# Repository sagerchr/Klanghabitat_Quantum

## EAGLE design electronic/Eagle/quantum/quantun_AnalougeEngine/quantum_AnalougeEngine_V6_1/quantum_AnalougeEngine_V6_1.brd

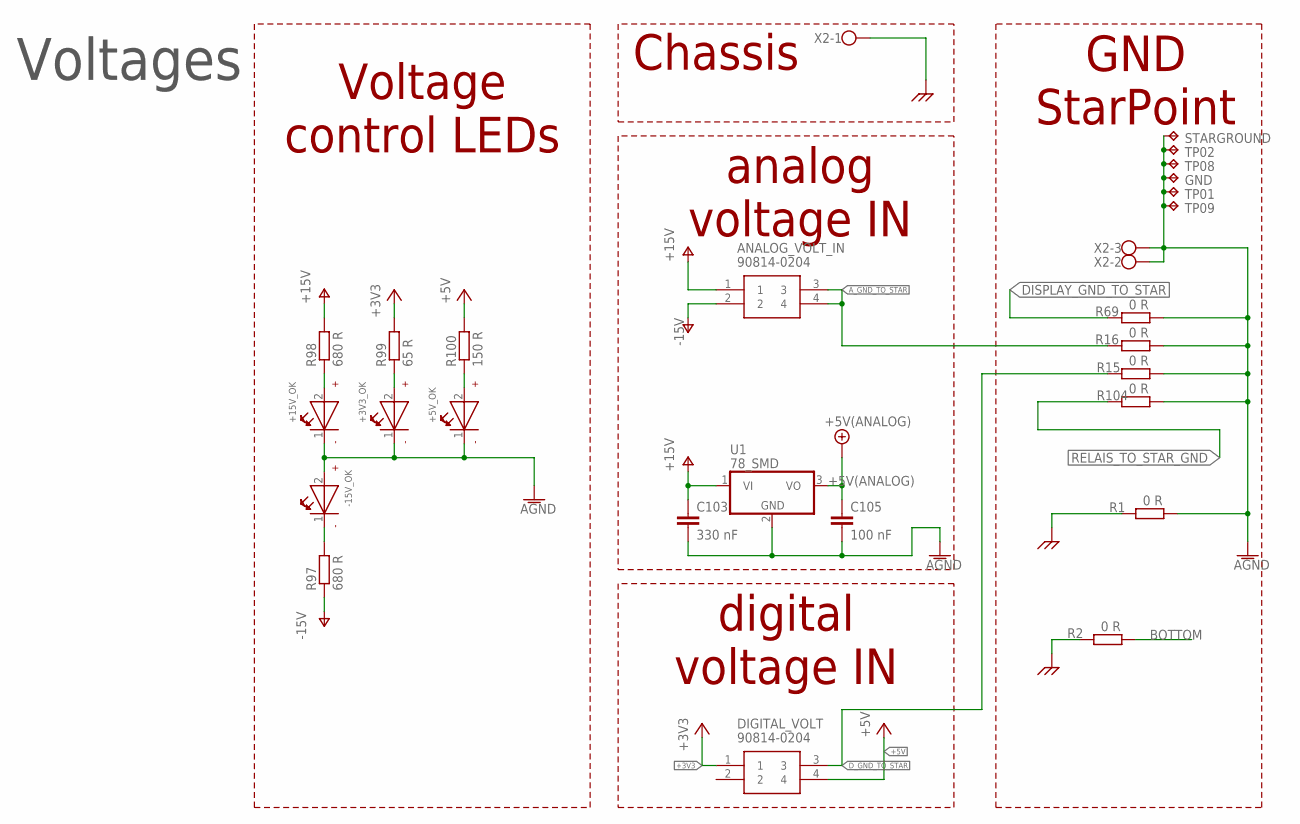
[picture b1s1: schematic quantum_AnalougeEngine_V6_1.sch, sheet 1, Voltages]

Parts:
+3V3_OK, +5V_OK, +15V_OK: LED_GREEN_SMD; WL-SMCW_0603
-15V_OK: LED_GREEN_SMD; WL-SMCW_0603
ANALOG_VOLT_IN: 90814-0204; MOLEX_90814-0204
C103: 330 nF; C0603
C105: 100 nF; C0603
DIGITAL_VOLT: 90814-0204; MOLEX_90814-0204
GND: TPTHT; THT_PIN
R1, R2, R15, R16, R69, R104: 0 R; R0603
R97, R98: 680 R; R0603
R99: 65 R; R0603
R100: 150 R; R0603
STARGROUND: TPTHT; THT_PIN
TP01, TP02, TP08, TP09: TPTHT; THT_PIN
U1: 78_SMD; TO252
X2: CONNECTOR_3POL; W237-103

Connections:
+3V3: DIGITAL_VOLT.1, R99.2; also elsewhere on the board
+5V: DIGITAL_VOLT.4, R100.2; also elsewhere on the board
+5V(ANALOG): C105.1, U1.3 (VO); also elsewhere on the board
AGND: +3V3_OK.1 (-), +5V_OK.1 (-), +15V_OK.1 (-), -15V_OK.2 (+), C103.2, C105.2, GND.P$1, R1.2, R15.2, R16.2, R69.2, R104.2, STARGROUND.P$1, TP01.P$1, TP02.P$1, TP08.P$1, TP09.P$1, U1.2 (GND), X2.2, X2.3; also elsewhere on the board
A_GND_TO_STAR: ANALOG_VOLT_IN.3, ANALOG_VOLT_IN.4, R16.1
BOTTOM: R2.2
CHASSIS: R1.1, R2.1, X2.1; also elsewhere on the board
DISPLAY_GND_TO_STAR: R69.1; also elsewhere on the board
D_GND_TO_STAR: DIGITAL_VOLT.3, R15.1
unnamed: -15V_OK.1 (-), R97.2
unnamed: +15V_OK.2 (+), R98.1
unnamed: +3V3_OK.2 (+), R99.1
unnamed: +5V_OK.2 (+), R100.1
RELAIS_TO_STAR_GND: R104.1; also elsewhere on the board
V+: ANALOG_VOLT_IN.1, C103.1, R98.2, U1.1 (VI); also elsewhere on the board
V-: ANALOG_VOLT_IN.2, R97.1; also elsewhere on the board

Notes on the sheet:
analog voltage IN
digital voltage IN
GND StarPoint
Chassis
Voltages
Voltage control LEDs

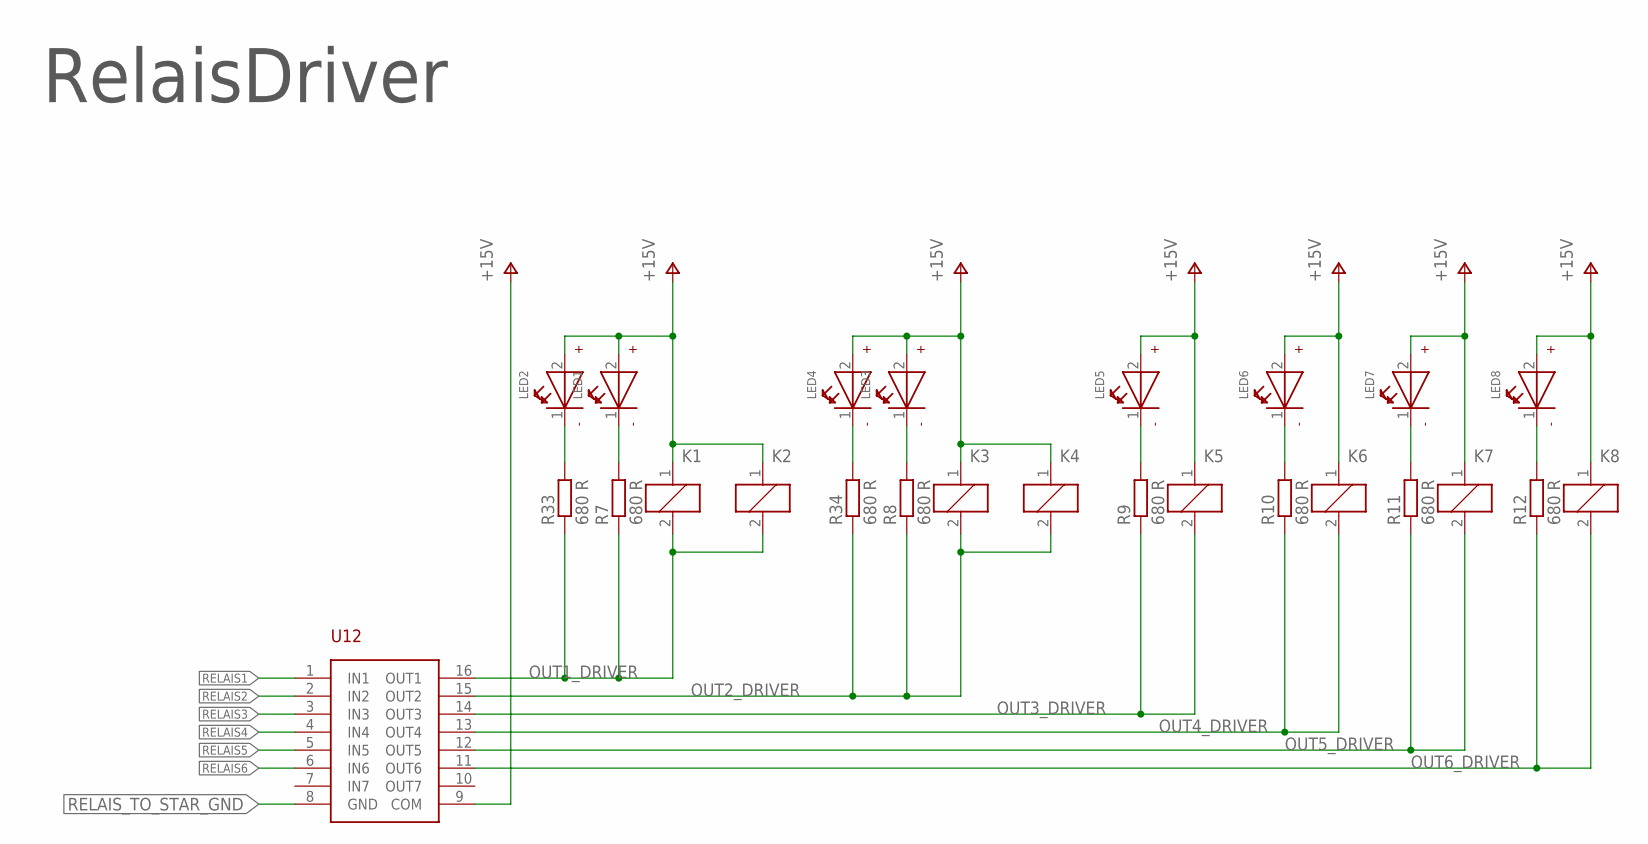
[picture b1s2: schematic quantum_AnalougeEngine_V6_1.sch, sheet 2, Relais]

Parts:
K1, K2, K3, K4, K5, K6, K7, K8: Relay; 351
LED1, LED2, LED3, LED4, LED5, LED6, LED7, LED8: LED_BLUE_SMD; WL-SMCW_0603
R7, R8, R9, R10, R11, R12, R33, R34: 680 R; R0603
U12: ULN2003; SOIC16

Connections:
unnamed: LED1.1 (-), R7.2
unnamed: LED3.1 (-), R8.2
unnamed: LED8.1 (-), R12.2
unnamed: LED7.1 (-), R11.2
unnamed: LED6.1 (-), R10.2
unnamed: LED5.1 (-), R9.2
unnamed: LED2.1 (-), R33.2
unnamed: LED4.1 (-), R34.2
OUT1_DRIVER: K1.2, K2.2, R7.1, R33.1, U12.16 (OUT1)
OUT2_DRIVER: K3.2, K4.2, R8.1, R34.1, U12.15 (OUT2)
OUT3_DRIVER: K5.2, R9.1, U12.14 (OUT3)
OUT4_DRIVER: K6.2, R10.1, U12.13 (OUT4)
OUT5_DRIVER: K7.2, R11.1, U12.12 (OUT5)
OUT6_DRIVER: K8.2, R12.1, U12.11 (OUT6)
RELAIS1: U12.1 (IN1); also elsewhere on the board
RELAIS2: U12.2 (IN2); also elsewhere on the board
RELAIS3: U12.3 (IN3); also elsewhere on the board
RELAIS4: U12.4 (IN4); also elsewhere on the board
RELAIS5: U12.5 (IN5); also elsewhere on the board
RELAIS6: U12.6 (IN6); also elsewhere on the board
RELAIS_TO_STAR_GND: U12.8 (GND); also elsewhere on the board
V+: K1.1, K2.1, K3.1, K4.1, K5.1, K6.1, K7.1, K8.1, LED1.2 (+), LED2.2 (+), LED3.2 (+), LED4.2 (+), LED5.2 (+), LED6.2 (+), LED7.2 (+), LED8.2 (+), U12.9 (COM); also elsewhere on the board

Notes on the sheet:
RelaisDriver

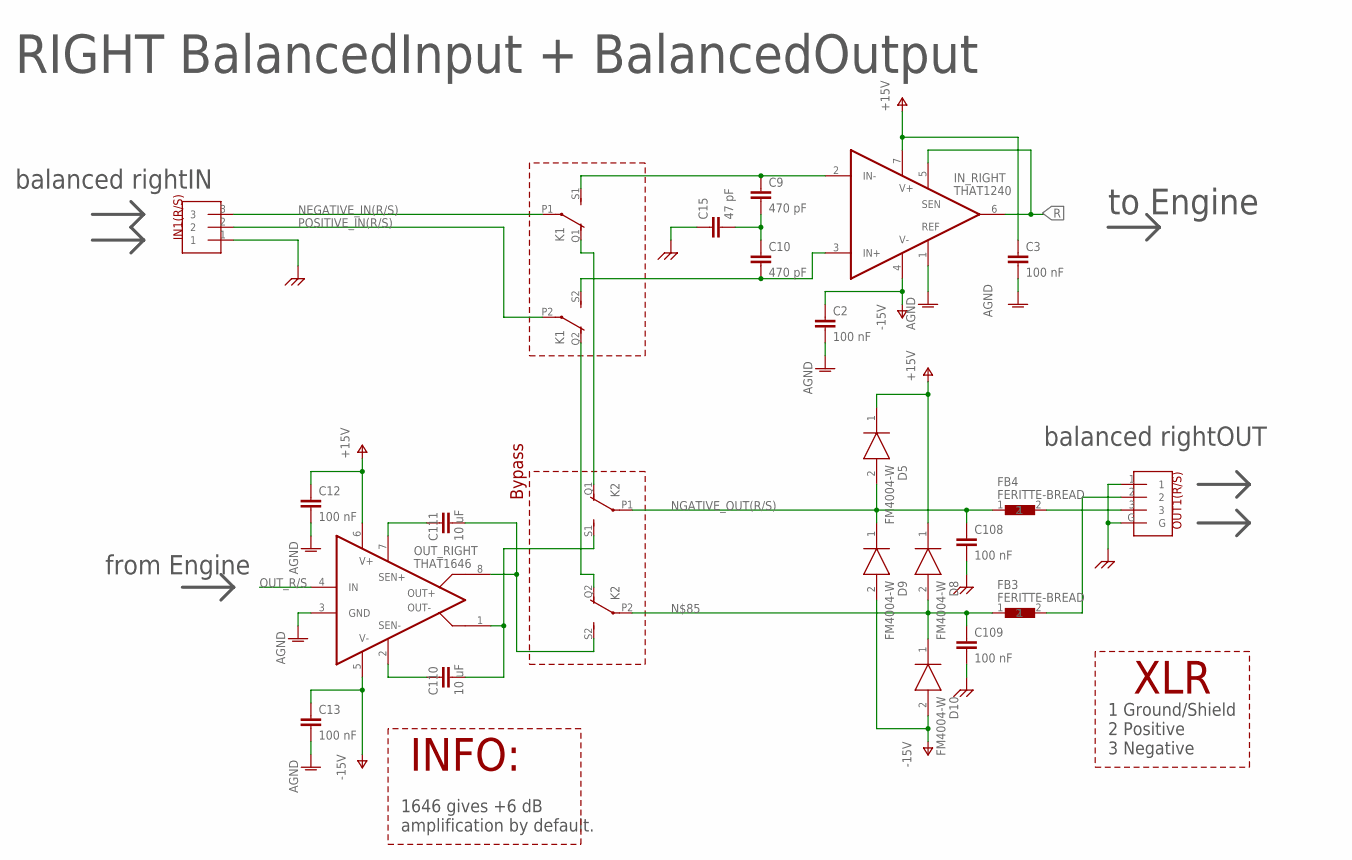
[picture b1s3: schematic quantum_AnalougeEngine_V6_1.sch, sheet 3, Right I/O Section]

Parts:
C2, C3, C12, C13, C108, C109: 100 nF; C0603
C9, C10: 470 pF; C0603
C15: 47 pF; C0603
C110, C111: 10 uF; C1206
D5, D8, D9, D10: FM4004-W; DIONM5025X231N
FB3, FB4: FERITTE-BREAD; BLM18KG102SH1J
IN1(R/S): NEUTRIK_NC3FAH
IN_RIGHT: THAT1240; SO08
K1, K2: Relay; 351
OUT1(R/S): NEUTRIK_NC3MAH
OUT_RIGHT: THAT1646; SO08

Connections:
AGND: C2.2, C3.2, C12.2, C13.2, IN_RIGHT.1 (REF), OUT_RIGHT.3 (GND); also elsewhere on the board
CHASSIS: C15.1, C108.2, C109.2, IN1(R/S).1, OUT1(R/S).1, OUT1(R/S).G; also elsewhere on the board
unnamed: C9.1, IN_RIGHT.2 (IN-), K1.S1 (S)
unnamed: C10.2, IN_RIGHT.3 (IN+), K1.S2 (S)
unnamed: C9.2, C10.1, C15.2
unnamed: K1.Q1 (O), K2.Q1 (O)
unnamed: K1.Q2 (O), K2.Q2 (O)
unnamed: FB4.2, OUT1(R/S).3
unnamed: C109.1, D8.2 (A), D10.1 (K), FB3.1, K2.P2
unnamed: C111.1, OUT_RIGHT.7 (SEN+)
unnamed: C110.1, OUT_RIGHT.2 (SEN-)
NEGATIVE_IN(R/S): IN1(R/S).3, K1.P1
NGATIVE_OUT(R/S): C108.1, D5.2 (A), D9.1 (K), FB4.1, K2.P1
OUT_R/S: OUT_RIGHT.4 (IN); also elsewhere on the board
POSITIVE_IN(R/S): IN1(R/S).2, K1.P2
POSITIVE_OUT(R/S): FB3.2, OUT1(R/S).2
R: IN_RIGHT.5 (SEN), IN_RIGHT.6 (OUT); also elsewhere on the board
R/S_OUT+: C111.2, K2.S2 (S), OUT_RIGHT.8 (OUT+)
R/S_OUT-: C110.2, K2.S1 (S), OUT_RIGHT.1 (OUT-)
V+: C3.1, C12.1, D5.1 (K), D8.1 (K), IN_RIGHT.7 (V+), OUT_RIGHT.6 (V+); also elsewhere on the board
V-: C2.1, C13.1, D9.2 (A), D10.2 (A), IN_RIGHT.4 (V-), OUT_RIGHT.5 (V-); also elsewhere on the board

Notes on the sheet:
RIGHT BalancedInput + BalancedOutput
balanced rightIN
balanced rightOUT
from Engine
to Engine
XLR
1 Ground/Shield 2 Positive 3 Negative
INFO:
1646 gives +6 dB amplification by default.
Bypass

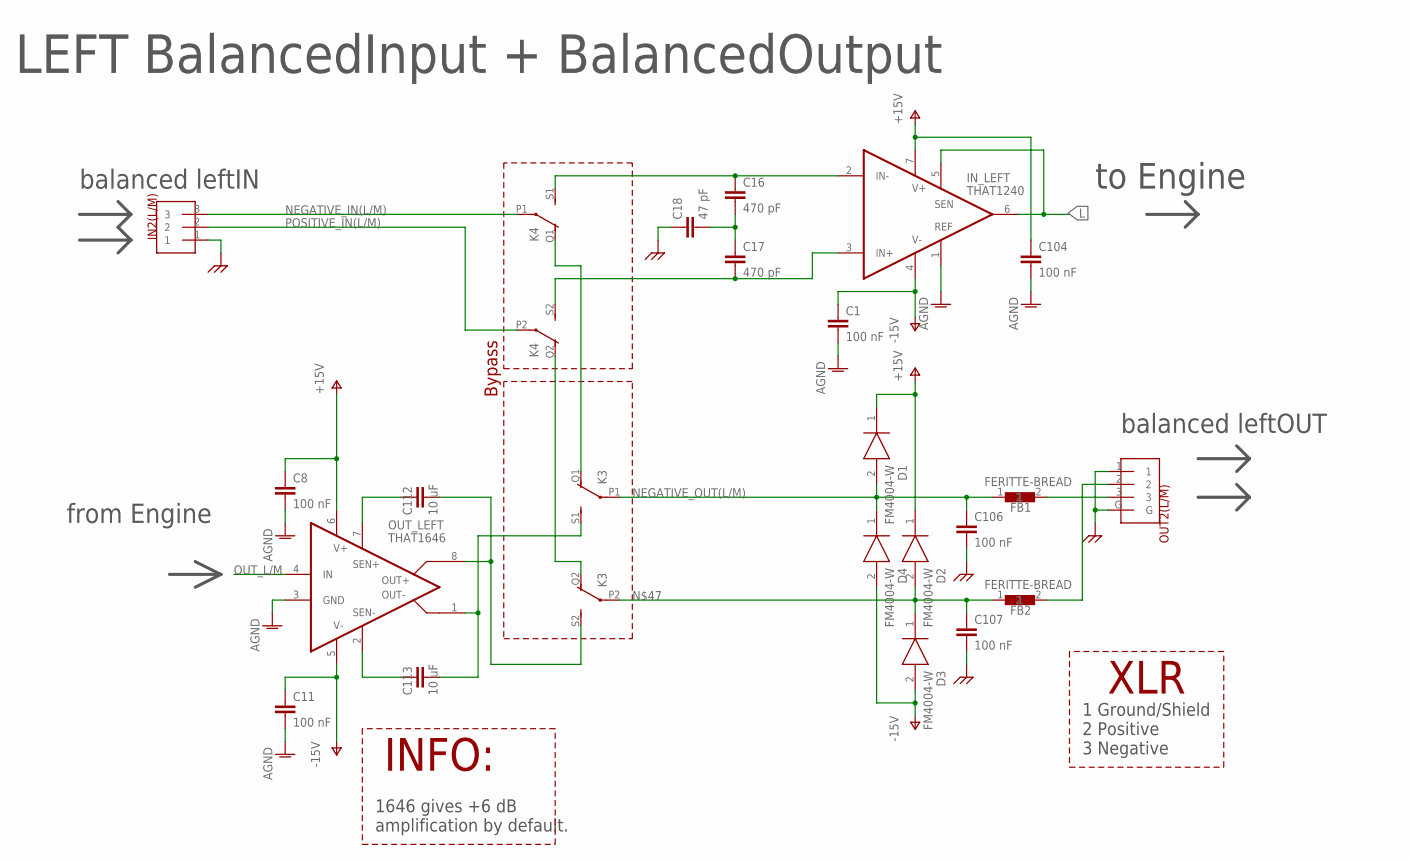
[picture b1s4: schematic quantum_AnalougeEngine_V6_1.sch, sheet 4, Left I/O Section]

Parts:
C1, C8, C11, C104, C106, C107: 100 nF; C0603
C16, C17: 470 pF; C0603
C18: 47 pF; C0603
C112, C113: 10 uF; C1206
D1, D2, D3, D4: FM4004-W; DIONM5025X231N
FB1, FB2: FERITTE-BREAD; BLM18KG102SH1J
IN2(L/M): NEUTRIK_NC3FAH
IN_LEFT: THAT1240; SO08
K3, K4: Relay; 351
OUT2(L/M): NEUTRIK_NC3MAH
OUT_LEFT: THAT1646; SO08

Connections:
AGND: C1.2, C8.2, C11.2, C104.2, IN_LEFT.1 (REF), OUT_LEFT.3 (GND); also elsewhere on the board
CHASSIS: C18.1, C106.2, C107.2, IN2(L/M).1, OUT2(L/M).1, OUT2(L/M).G; also elsewhere on the board
L: IN_LEFT.5 (SEN), IN_LEFT.6 (OUT); also elsewhere on the board
L/M_OUT+: C112.2, K3.S2 (S), OUT_LEFT.8 (OUT+)
L/M_OUT-: C113.2, K3.S1 (S), OUT_LEFT.1 (OUT-)
unnamed: C17.2, IN_LEFT.3 (IN+), K4.S2 (S)
unnamed: C16.2, C17.1, C18.2
unnamed: C16.1, IN_LEFT.2 (IN-), K4.S1 (S)
unnamed: K3.Q1 (O), K4.Q1 (O)
unnamed: K3.Q2 (O), K4.Q2 (O)
unnamed: FB1.2, OUT2(L/M).3
unnamed: C107.1, D2.2 (A), D3.1 (K), FB2.1, K3.P2
unnamed: C113.1, OUT_LEFT.2 (SEN-)
unnamed: C112.1, OUT_LEFT.7 (SEN+)
NEGATIVE_IN(L/M): IN2(L/M).3, K4.P1
NEGATIVE_OUT(L/M): C106.1, D1.2 (A), D4.1 (K), FB1.1, K3.P1
OUT_L/M: OUT_LEFT.4 (IN); also elsewhere on the board
POSITIVE_IN(L/M): IN2(L/M).2, K4.P2
POSITIVE_OUT(L/M): FB2.2, OUT2(L/M).2
V+: C8.1, C104.1, D1.1 (K), D2.1 (K), IN_LEFT.7 (V+), OUT_LEFT.6 (V+); also elsewhere on the board
V-: C1.1, C11.1, D3.2 (A), D4.2 (A), IN_LEFT.4 (V-), OUT_LEFT.5 (V-); also elsewhere on the board

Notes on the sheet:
balanced leftIN
balanced leftOUT
from Engine
to Engine
LEFT BalancedInput + BalancedOutput
XLR
1 Ground/Shield 2 Positive 3 Negative
INFO:
1646 gives +6 dB amplification by default.
Bypass

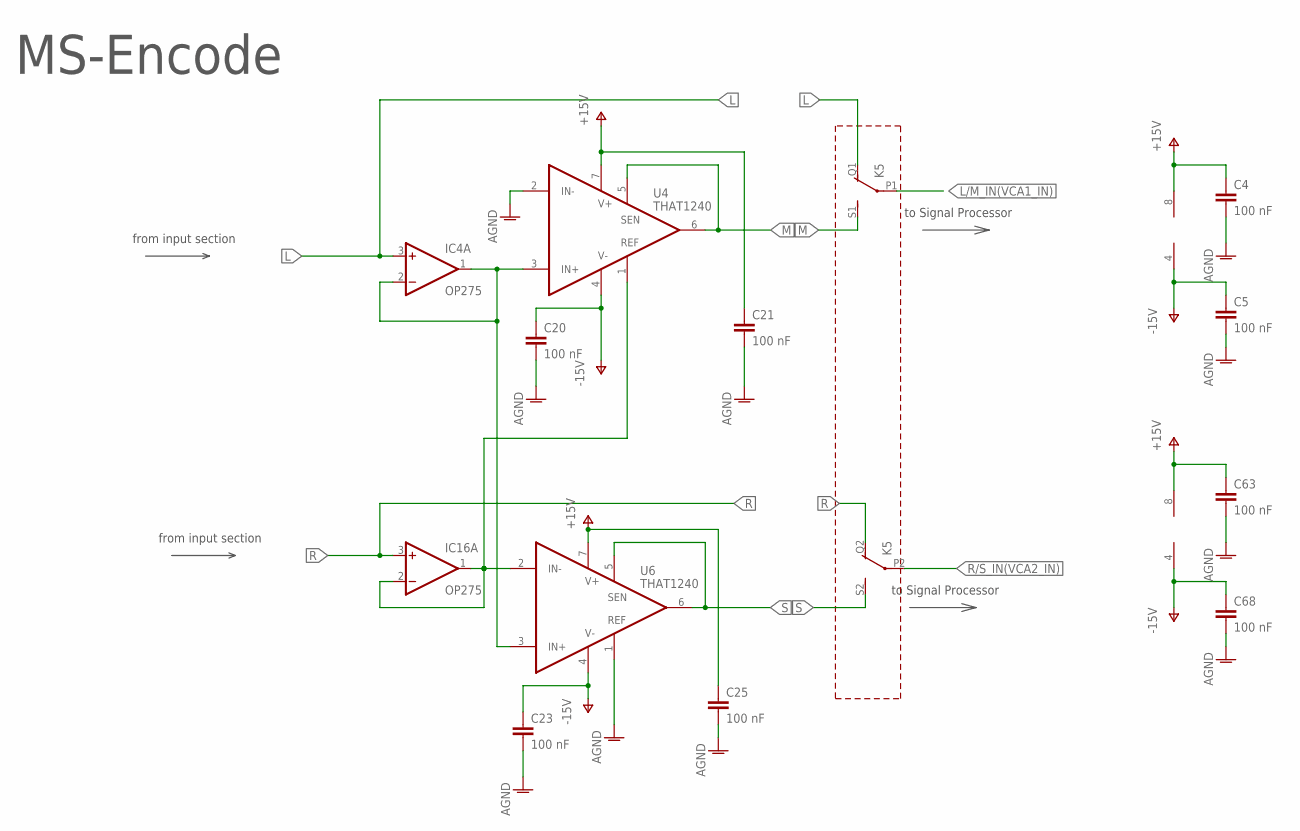
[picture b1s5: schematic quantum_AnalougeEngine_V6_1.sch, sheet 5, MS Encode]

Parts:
C4, C5, C20, C21, C23, C25, C63, C68: 100 nF; C0603
IC4, IC16: OP275; SOIC8
K5: Relay; 351
U4, U6: THAT1240; SO08

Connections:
AGND: C4.2, C5.2, C20.2, C21.2, C23.2, C25.2, C63.2, C68.2, U4.2 (IN-), U6.1 (REF); also elsewhere on the board
L: IC4.3 (+IN), K5.Q1 (O); also elsewhere on the board
L/M_IN(VCA1_IN): K5.P1; also elsewhere on the board
M: K5.S1 (S), U4.5 (SEN), U4.6 (OUT)
unnamed: IC4.1 (OUT), IC4.2 (-IN), U4.3 (IN+), U6.3 (IN+)
unnamed: IC16.1 (OUT), IC16.2 (-IN), U4.1 (REF), U6.2 (IN-)
R: IC16.3 (+IN), K5.Q2 (O); also elsewhere on the board
R/S_IN(VCA2_IN): K5.P2; also elsewhere on the board
S: K5.S2 (S), U6.5 (SEN), U6.6 (OUT)
V+: C4.1, C21.1, C25.1, C63.1, IC4.8 (V+), IC16.8 (V+), U4.7 (V+), U6.7 (V+); also elsewhere on the board
V-: C5.1, C20.1, C23.1, C68.1, IC4.4 (V-), IC16.4 (V-), U4.4 (V-), U6.4 (V-); also elsewhere on the board

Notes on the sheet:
to Signal Processor
MS-Encode
from input section

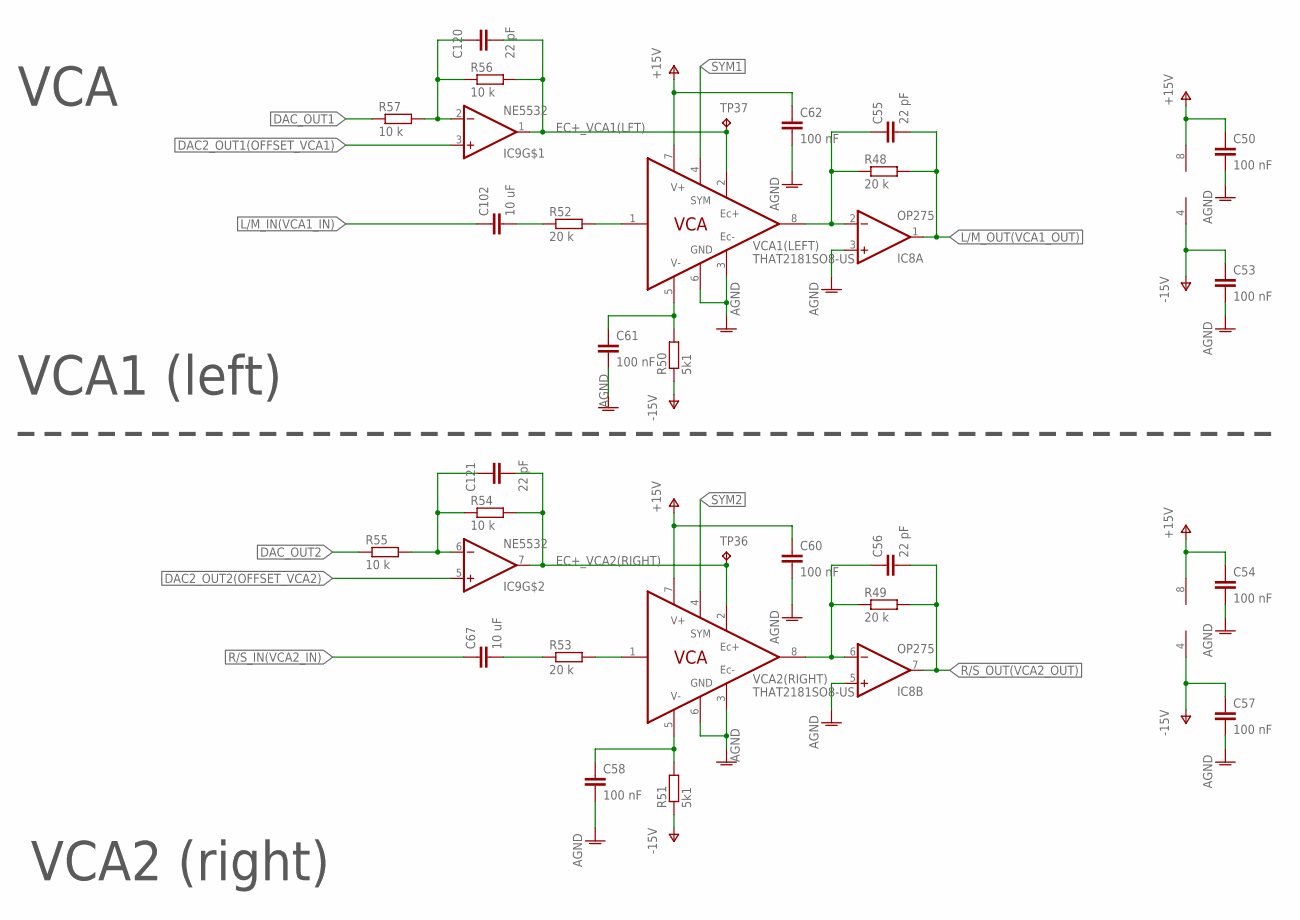
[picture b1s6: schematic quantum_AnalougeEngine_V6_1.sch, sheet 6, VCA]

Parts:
C50, C53, C54, C57, C58, C60, C61, C62: 100 nF; C0603
C55, C56, C120, C121: 22 pF; C0603
C67, C102: 10 uF; C1206
IC8: OP275; SOIC8
IC9: NE5532; SOIC8
R48, R49, R52, R53: 20 k; R0603
R50, R51: 5k1; R0603
R54, R55, R56, R57: 10 k; R0603
TP36, TP37: TPTHT; THT_PIN
VCA1(LEFT), VCA2(RIGHT): THAT2181SO8-US; SO08

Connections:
AGND: C50.2, C53.2, C54.2, C57.2, C58.2, C60.2, C61.2, C62.2, IC8.3 (+IN), IC8.5 (+IN), VCA1(LEFT).3 (EC-), VCA1(LEFT).6 (GND), VCA2(RIGHT).3 (EC-), VCA2(RIGHT).6 (GND); also elsewhere on the board
DAC2_OUT1(OFFSET_VCA1): IC9.3 (+IN); also elsewhere on the board
DAC2_OUT2(OFFSET_VCA2): IC9.5 (+IN); also elsewhere on the board
DAC_OUT1: R57.1; also elsewhere on the board
DAC_OUT2: R55.1; also elsewhere on the board
EC+_VCA1(LFT): C120.2, IC9.1 (OUT), R56.2, TP37.P$1, VCA1(LEFT).2 (EC+)
EC+_VCA2(RIGHT): C121.2, IC9.7 (OUT), R54.2, TP36.P$1, VCA2(RIGHT).2 (EC+)
L/M_IN(VCA1_IN): C102.1; also elsewhere on the board
L/M_OUT(VCA1_OUT): C55.2, IC8.1 (OUT), R48.2; also elsewhere on the board
unnamed: C120.1, IC9.2 (-IN), R56.1, R57.2
unnamed: C55.1, IC8.2 (-IN), R48.1, VCA1(LEFT).8 (OUT)
unnamed: R52.2, VCA1(LEFT).1 (IN)
unnamed: C102.2, R52.1
unnamed: C56.1, IC8.6 (-IN), R49.1, VCA2(RIGHT).8 (OUT)
unnamed: C58.1, R51.2, VCA2(RIGHT).5 (V-)
unnamed: C67.2, R53.1
unnamed: R53.2, VCA2(RIGHT).1 (IN)
unnamed: C61.1, R50.2, VCA1(LEFT).5 (V-)
unnamed: C121.1, IC9.6 (-IN), R54.1, R55.2
R/S_IN(VCA2_IN): C67.1; also elsewhere on the board
R/S_OUT(VCA2_OUT): C56.2, IC8.7 (OUT), R49.2; also elsewhere on the board
SYM1: VCA1(LEFT).4 (SYM); also elsewhere on the board
SYM2: VCA2(RIGHT).4 (SYM); also elsewhere on the board
V+: C50.1, C54.1, C60.1, C62.1, IC8.8 (V+), IC9.8 (V+), VCA1(LEFT).7 (V+), VCA2(RIGHT).7 (V+); also elsewhere on the board
V-: C53.1, C57.1, IC8.4 (V-), IC9.4 (V-), R50.1, R51.1; also elsewhere on the board

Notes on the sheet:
VCA
VCA1 (left)
VCA2 (right)

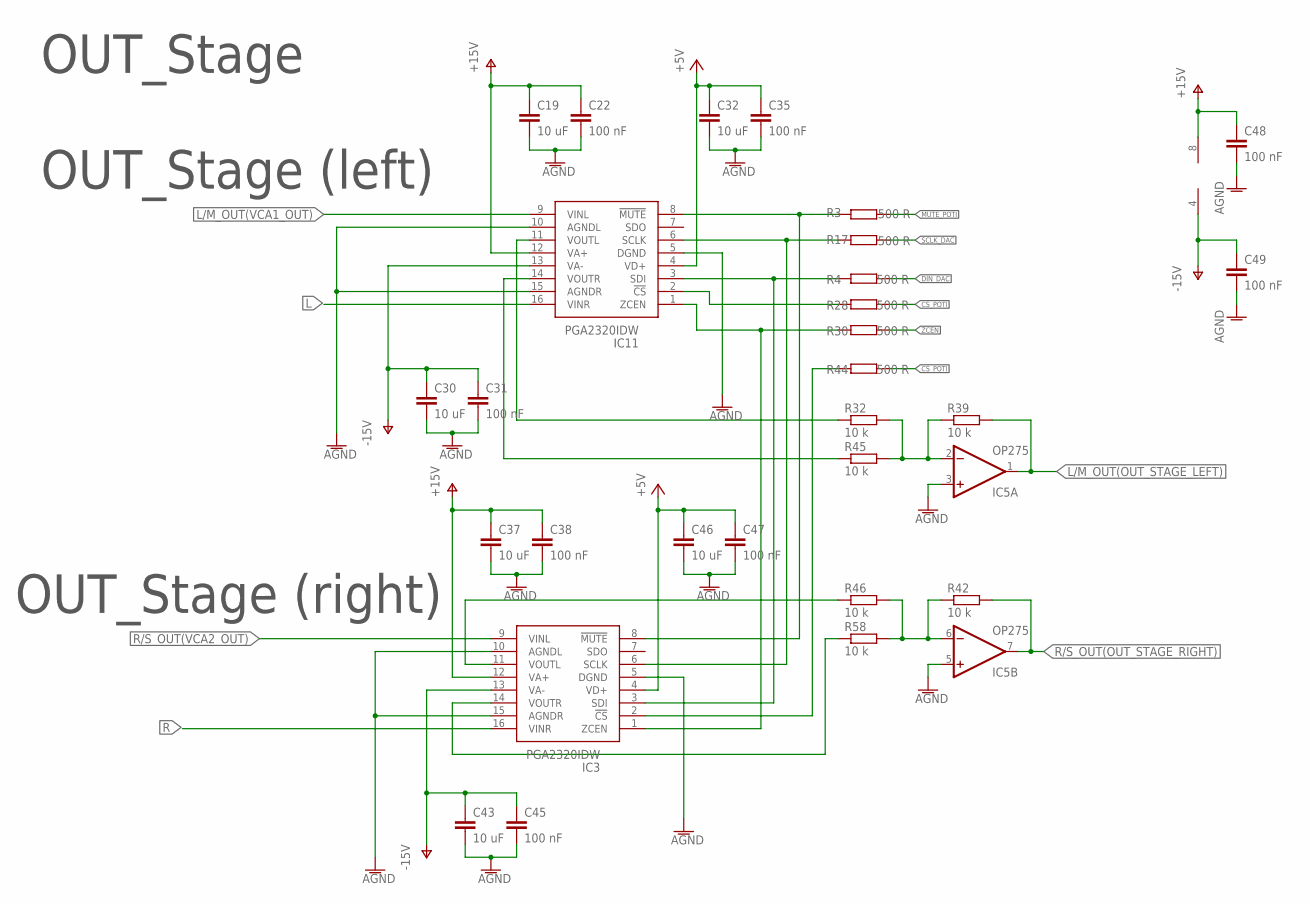
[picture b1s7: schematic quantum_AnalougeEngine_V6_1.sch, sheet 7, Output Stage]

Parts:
C19, C30, C32, C37, C43, C46: 10 uF; C1206
C22, C31, C35, C38, C45, C47, C48, C49: 100 nF; C0603
IC3, IC11: PGA2320IDW; SOIC127P1030X265-16N
IC5: OP275; SOIC8
R3, R4, R17, R28, R30, R44: 500 R; R0603
R32, R39, R42, R45, R46, R58: 10 k; R0603

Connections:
+5V: C32.1, C35.1, C46.1, C47.1, IC3.4 (VD+), IC11.4 (VD+); also elsewhere on the board
AGND: C19.2, C22.2, C30.2, C31.2, C32.2, C35.2, C37.2, C38.2, C43.2, C45.2, C46.2, C47.2, C48.2, C49.2, IC3.5 (DGND), IC3.10 (AGNDL), IC3.15 (AGNDR), IC5.3 (+IN), IC5.5 (+IN), IC11.5 (DGND), IC11.10 (AGNDL), IC11.15 (AGNDR); also elsewhere on the board
CS_POTI: R28.2, R44.2; also elsewhere on the board
DIN_DAC: R4.2; also elsewhere on the board
L: IC11.16 (VINR); also elsewhere on the board
L/M_OUT(OUT_STAGE_LEFT): IC5.1 (OUT), R39.2; also elsewhere on the board
L/M_OUT(OUT_STAGE_LEFT)1: IC3.11 (VOUTL), R46.1
L/M_OUT(VCA1_OUT): IC11.9 (VINL); also elsewhere on the board
MUTE_POTI: R3.2; also elsewhere on the board
unnamed: IC5.2 (-IN), R32.2, R39.1, R45.2
unnamed: IC3.8 (!MUTE), IC11.8 (!MUTE), R3.1
unnamed: IC3.6 (SCLK), IC11.6 (SCLK), R17.1
unnamed: IC3.3 (SDI), IC11.3 (SDI), R4.1
unnamed: IC11.2 (!CS), R28.1
unnamed: IC3.1 (ZCEN), IC11.1 (ZCEN), R30.1
unnamed: IC11.11 (VOUTL), R32.1
unnamed: IC11.14 (VOUTR), R45.1
unnamed: IC5.6 (-IN), R42.1, R46.2, R58.2
unnamed: IC3.14 (VOUTR), R58.1
unnamed: IC3.2 (!CS), R44.1
R: IC3.16 (VINR); also elsewhere on the board
R/S_OUT(OUT_STAGE_RIGHT): IC5.7 (OUT), R42.2; also elsewhere on the board
R/S_OUT(VCA2_OUT): IC3.9 (VINL); also elsewhere on the board
SCLK_DAC: R17.2; also elsewhere on the board
V+: C19.1, C22.1, C37.1, C38.1, C48.1, IC3.12 (VA+), IC5.8 (V+), IC11.12 (VA+); also elsewhere on the board
V-: C30.1, C31.1, C43.1, C45.1, C49.1, IC3.13 (VA-), IC5.4 (V-), IC11.13 (VA-); also elsewhere on the board
ZCEN: R30.2; also elsewhere on the board

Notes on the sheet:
OUT_Stage
OUT_Stage (left)
OUT_Stage (right)

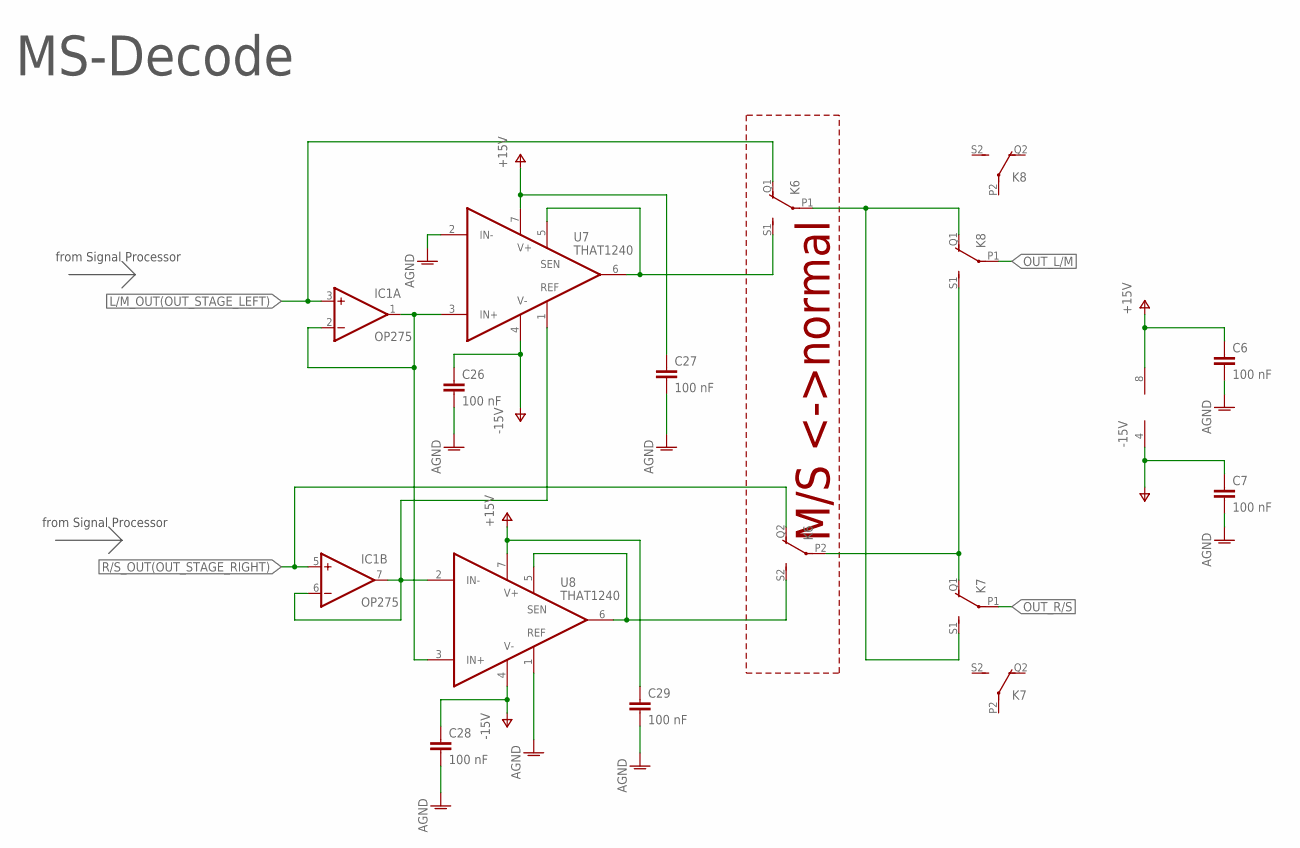
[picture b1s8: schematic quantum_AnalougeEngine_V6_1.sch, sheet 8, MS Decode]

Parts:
C6, C7, C26, C27, C28, C29: 100 nF; C0603
IC1: OP275; SOIC8
K6, K7, K8: Relay; 351
U7, U8: THAT1240; SO08

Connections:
AGND: C6.2, C7.2, C26.2, C27.2, C28.2, C29.2, U7.2 (IN-), U8.1 (REF); also elsewhere on the board
L/M_OUT(OUT_STAGE_LEFT): IC1.3 (+IN), K6.Q1 (O); also elsewhere on the board
M1: K6.S1 (S), U7.5 (SEN), U7.6 (OUT)
unnamed: K6.P1, K7.S1 (S), K8.Q1 (O)
unnamed: K6.P2, K7.Q1 (O), K8.S1 (S)
unnamed: IC1.6 (-IN), IC1.7 (OUT), U7.1 (REF), U8.2 (IN-)
unnamed: IC1.1 (OUT), IC1.2 (-IN), U7.3 (IN+), U8.3 (IN+)
OUT_L/M: K8.P1; also elsewhere on the board
OUT_R/S: K7.P1; also elsewhere on the board
R/S_OUT(OUT_STAGE_RIGHT): IC1.5 (+IN), K6.Q2 (O); also elsewhere on the board
S1: K6.S2 (S), U8.5 (SEN), U8.6 (OUT)
V+: C6.1, C27.1, C29.1, IC1.8 (V+), U7.7 (V+), U8.7 (V+); also elsewhere on the board
V-: C7.1, C26.1, C28.1, IC1.4 (V-), U7.4 (V-), U8.4 (V-); also elsewhere on the board

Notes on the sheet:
from Signal Processor
MS-Decode
M/S <->normal

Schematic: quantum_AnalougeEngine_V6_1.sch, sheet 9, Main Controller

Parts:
C36, C71, C72: 2.2 uF; C1206
C39, C99: 10 uF; C1206
C44, C59, C73, C74, C75, C76, C77, C78, C79, C80, C81, C82, C83, C84, C85: 100 nF; C0603
C65, C66: 2.7 pF; C0603
C69, C70: 4.3 pF; C0603
C119: 4.7 uF; C1206
DEBUG1, DEBUG2: TPTHT; THT_PIN
DISPLAY1: 90814-0204; MOLEX_90814-0204
FB6, FB7: FERITTE-BREAD; BLM18KG102SH1J
IC10: STM32F767ZIT6; QFP50P2200X2200X160-144N
IC12: ESDA6V1BC6; SOT95P280X145-6N
LD1: LED_YELOW_SMD; WL-SMCW_0603
LD2: LED_RED_SMD; WL-SMCW_0603
LD3: LED_GREEN_SMD; WL-SMCW_0603
PROG.: 90814-0204; MOLEX_90814-0204
R5, R6, R13: 680 R; R0603
R19, R78: 10 k; R0603
R31, R36, R37: 0 R; R0603
S1: PTS647SN50SMTR2LFS
TP05, TP06, TP07: TPTHT; THT_PIN
X1: USB_B_CONNECTOR; SMARTPRJ_PN61729
Y1: NX3215SA-32.768K-STD-MUA-8; NX3215SA
Y2: NX3225GD-8MHZ-STD-CRA-3; RESC3226X100N

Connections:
8MHZ_CRYSTAL_A: C70.1, IC10.23 (PH0), Y2.1
8MHZ_CRYSTAL_B: C69.1, IC10.24 (PH1), Y2.2
32.768KHZ_A: C66.1, IC10.8 (PC14), Y1.1
32.768KHZ_B: C65.1, IC10.9 (PC15), Y1.2
+3V3: C59.2, C73.1, C74.1, C75.1, C76.1, C77.1, C78.1, C79.1, C81.2, C82.2, C83.1, C84.1, C85.1, C119.2, FB6.1, IC10.6 (VBAT), IC10.17 (VDD_1), IC10.30 (VDD_2), IC10.39 (VDD_3), IC10.52 (VDD_4), IC10.62 (VDD_5), IC10.72 (VDD_6), IC10.84 (VDD_7), IC10.95 (VDDUSB), IC10.108 (VDD_8), IC10.121 (VDDSDMMC), IC10.131 (VDD_9), IC10.143 (PDR_ON), IC10.144 (VDD_10); also elsewhere on the board
+3V3_SIG: IC10.47 (PB1)
+5V: C99.1, FB7.2; also elsewhere on the board
+5V_SIG: IC10.26 (PC0)
+12V_SIG: IC10.42 (PA6)
+15V_SIG: IC10.34 (PA0)
-15V_SIG: IC10.37 (PA3)
AGND: C36.1, C44.1, C59.1, C65.2, C66.2, C69.2, C70.2, C71.2, C72.2, C73.2, C74.2, C75.2, C76.2, C77.2, C78.2, C79.2, C80.1, C81.1, C82.1, C83.2, C84.2, C85.2, C119.1, IC10.16 (VSS_1), IC10.31 (VSSA), IC10.38 (VSS_2), IC10.51 (VSS_3), IC10.61 (VSS_4), IC10.83 (VSS_5), IC10.94 (VSS_6), IC10.107 (VSS_7), IC10.120 (VSS_8), IC10.130 (VSS_9), IC12.2, IC12.5, PROG..4, R5.1, R6.1, R13.1, R78.2, S1.1, S1.2, X1.4; also elsewhere on the board
BOOT0: C36.2, IC10.138 (BOOT0), R31.1, R78.1
BUSY: IC10.88 (PG3); also elsewhere on the board
CHASSIS: X1.P$1, X1.P$2; also elsewhere on the board
CS: IC10.123 (PD7); also elsewhere on the board
CS_DAC1: IC10.134 (PB4); also elsewhere on the board
CS_POTI: IC10.135 (PB5); also elsewhere on the board
CV_A_B: IC10.113 (PC12); also elsewhere on the board
DAC_OUT1: IC10.40 (PA4); also elsewhere on the board
DAC_OUT2: IC10.41 (PA5); also elsewhere on the board
DB0: IC10.141 (PE0); also elsewhere on the board
DB1: IC10.142 (PE1); also elsewhere on the board
DB2: IC10.1 (PE2); also elsewhere on the board
DB3: IC10.2 (PE3); also elsewhere on the board
DB4: IC10.3 (PE4); also elsewhere on the board
DB5: IC10.4 (PE5); also elsewhere on the board
DB6: IC10.5 (PE6); also elsewhere on the board
DB7: IC10.58 (PE7); also elsewhere on the board
DB8: IC10.59 (PE8); also elsewhere on the board
DB9: IC10.60 (PE9); also elsewhere on the board
DB10: IC10.63 (PE10); also elsewhere on the board
DB11: IC10.64 (PE11); also elsewhere on the board
DB12: IC10.65 (PE12); also elsewhere on the board
DB13: IC10.66 (PE13); also elsewhere on the board
DB14: IC10.67 (PE14); also elsewhere on the board
DB15: IC10.68 (PE15); also elsewhere on the board
DEBUG1: DEBUG1.P$1, IC10.21 (PF9)
DEBUG2: DEBUG2.P$1, IC10.115 (PD1)
DIN_DAC: IC10.29 (PC3); also elsewhere on the board
DISPLAY_GND_TO_STAR: C39.2, C99.2, DISPLAY1.4; also elsewhere on the board
FRST: IC10.122 (PD6); also elsewhere on the board
LD1: IC10.46 (PB0), LD1.2 (+)
LD2: IC10.137 (PB7), LD2.2 (+)
LD3: IC10.75 (PB14), LD3.2 (+)
MUTE_POTI: IC10.79 (PD10); also elsewhere on the board
unnamed: LD1.1 (-), R5.2
unnamed: IC10.101 (PA9), R19.1
unnamed: LD2.1 (-), R6.2
unnamed: C71.1, IC10.71 (VCAP_1)
unnamed: C72.1, IC10.106 (VCAP_2)
unnamed: LD3.1 (-), R13.2
unnamed: IC10.81 (PD12), R31.2
unnamed: C39.1, DISPLAY1.3, FB7.1
unnamed: C80.2, FB6.2, IC10.32 (VREF+), IC10.33 (VDDA)
NRST: C44.2, IC10.25 (NRST), PROG..2, S1.3, S1.4; also elsewhere on the board
OS0: IC10.98 (PC8); also elsewhere on the board
OS1: IC10.99 (PC9); also elsewhere on the board
OS2: IC10.111 (PC10); also elsewhere on the board
PB12: IC10.73 (PB12), TP05.P$1
RANGE: IC10.112 (PC11); also elsewhere on the board
RD: IC10.116 (PD2); also elsewhere on the board
RELAIS1: IC10.57 (PG1); also elsewhere on the board
RELAIS2: IC10.56 (PG0); also elsewhere on the board
RELAIS3: IC10.132 (PG15); also elsewhere on the board
RELAIS4: IC10.125 (PG10); also elsewhere on the board
RELAIS5: IC10.127 (PG12); also elsewhere on the board
RELAIS6: IC10.124 (PG9); also elsewhere on the board
RESET: IC10.87 (PG2); also elsewhere on the board
RMII_CRS_DV: IC10.43 (PA7); also elsewhere on the board
RMII_MDC: IC10.27 (PC1); also elsewhere on the board
RMII_MDIO: IC10.36 (PA2); also elsewhere on the board
RMII_REF_CLK: IC10.35 (PA1); also elsewhere on the board
RMII_RXD0: IC10.44 (PC4); also elsewhere on the board
RMII_RXD1: IC10.45 (PC5); also elsewhere on the board
RMII_TXD0: IC10.128 (PG13); also elsewhere on the board
RMII_TXD1: IC10.74 (PB13); also elsewhere on the board
RMII_TX_EN: IC10.126 (PG11); also elsewhere on the board
SCLK_DAC: IC10.69 (PB10); also elsewhere on the board
SWCLK: IC10.109 (PA14), PROG..1
SWDIO: IC10.105 (PA13), PROG..3
USART1_RX: IC10.76 (PB15)
USART1_TX: IC10.136 (PB6)
USART3_RX: IC10.77 (PD8), TP06.P$1
USART3_TX: IC10.78 (PD9), TP07.P$1
USART6_RX: DISPLAY1.2, IC10.97 (PC7)
USART6_TX: DISPLAY1.1, IC10.96 (PC6)
USB_ID: IC10.102 (PA10)
USB_N: IC10.103 (PA11), R36.1
USB_N_AFTER: IC12.3, R36.2, X1.2
USB_OVERCURRENT: IC10.92 (PG7)
USB_P: IC10.104 (PA12), R37.1
USB_POWERSWITCHON: IC10.91 (PG6)
USB_P_AFTER: IC12.6, R37.2, X1.3
USB_SOF: IC10.100 (PA8)
USB_VBUS: IC12.1, R19.2, X1.1
ZCEN: IC10.80 (PD11); also elsewhere on the board

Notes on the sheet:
prg.adapter
8 MHZ
debug LEDs
USB port
Main Controller
reset switch
32.768 kHz
diff pair
display1 adapter

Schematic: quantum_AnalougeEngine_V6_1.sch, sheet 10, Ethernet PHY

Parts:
C40, C100: 30 pF; C0603
C86, C87, C90, C92, C93, C94: 100 nF; C0603
C88: 1 uF; C0603
C89: 470 pF; C0603
C91: 10 uF; C1206
C101: 4.7 uF; C1206
FB5: 0 R; BLM18KG102SH1J
IC6: LAN8742A-CZ-TR; QFN50P400X400X100-25N
IC13: USBLC6-4SC6; SOT95P280X145-6N
J1: GWLEX-SMT-S988G_Y; GWLEXSMTS988GY
R18, R20, R21, R23, R27, R85: 10 k; R0603
R22: 1k5; R0603
R24, R25, R26: 33 R; R0603
R29, R88, R89, R90: 75 R; R0603
R77: 12k1; R0603
R79, R80, R81, R82: 50 R; R0603
R83, R84: 270 R; R0603
R91: 0 R; R0603
T1: H1102NL; SOIC127P940X597-16N
Y3: ABLS2-25.000MHZ-D4YF-T; ABLS

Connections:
+3V3: C86.2, C87.2, C90.2, C91.1, C92.2, C93.2, FB5.1, IC6.1 (VDD2A), IC6.9 (VDDIO), IC6.19 (VDD1A), R18.1, R20.1, R21.1, R22.1, R23.2, T1.2 (CT_1), T1.7 (CT_2); also elsewhere on the board
AGND: C40.1, C86.1, C87.1, C88.1, C89.1, C90.1, C91.2, C92.1, C93.1, C94.1, C100.1, IC6.25 (EP_VSS), IC13.2 (GND), R27.1, R77.2, R83.1, R84.1, R85.1; also elsewhere on the board
CHASSIS: R91.1; also elsewhere on the board
ETHERNET_CHASSIS: C101.2, J1.MP1 (13), J1.MP2 (14), R91.2
LED1: IC6.3 (LED1/NINT/NPME/!REGOFF), J1.10 (YELLOW_A)
LED2: IC6.2 (LED2/NINT/NPME/!NINTSEL), J1.12 (GREEN_A), R85.2
unnamed: IC6.7 (RXD1/!MODE1), R18.2, R24.2
unnamed: IC6.8 (RXD0/!MODE0), R20.2, R25.2
unnamed: IC6.11 (CRS_DV/!MODE2), R21.2, R26.2
unnamed: IC6.10 (RXER/!PHYAD0), R27.2
unnamed: IC6.24 (RBIAS), R77.1
unnamed: C88.2, C89.2, IC6.6 (VDDCR)
unnamed: J1.1, T1.16 (TX+)
unnamed: J1.2, T1.14 (TX-)
unnamed: J1.3, T1.11 (RX+)
unnamed: C94.2, FB5.2, IC13.5 (VBUS), R79.2, R80.2, R81.2, R82.2
unnamed: J1.6, T1.9 (RX-)
unnamed: J1.11 (GREEN_K), R84.2
unnamed: J1.9 (YELLOW_K), R83.2
unnamed: C40.2, IC6.4 (XTAL2), Y3.1
unnamed: C100.2, IC6.5 (XTAL1/CLKIN), Y3.2
unnamed: J1.7, R29.2
unnamed: J1.8, R88.2
unnamed: R89.2, T1.12 (NC_4)
unnamed: R90.2, T1.15 (NC_6)
unnamed: C101.1, R29.1, R88.1, R89.1, R90.1
NRST: IC6.15 (NRST); also elsewhere on the board
RD_N: IC6.22 (RXN), IC13.6 (I/O4), R82.1, T1.8 (RD-)
RD_P: IC6.23 (RXP), IC13.1 (I/O1), R81.1, T1.6 (RD+)
RMII_CRS_DV: R26.1; also elsewhere on the board
RMII_MDC: IC6.13 (MDC); also elsewhere on the board
RMII_MDIO: IC6.12 (MDIO), R22.2; also elsewhere on the board
RMII_REF_CLK: IC6.14 (NINT/REFCLKO), R23.1; also elsewhere on the board
RMII_RXD0: R25.1; also elsewhere on the board
RMII_RXD1: R24.1; also elsewhere on the board
RMII_TXD0: IC6.17 (TXD0); also elsewhere on the board
RMII_TXD1: IC6.18 (TXD1); also elsewhere on the board
RMII_TX_EN: IC6.16 (TXEN); also elsewhere on the board
TD_N: IC6.20 (TXN), IC13.4 (I/O3), R80.1, T1.3 (TD-)
TD_P: IC6.21 (TXP), IC13.3 (I/O2), R79.1, T1.1 (TD+)

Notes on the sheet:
Ethernet PHY
diff pair
